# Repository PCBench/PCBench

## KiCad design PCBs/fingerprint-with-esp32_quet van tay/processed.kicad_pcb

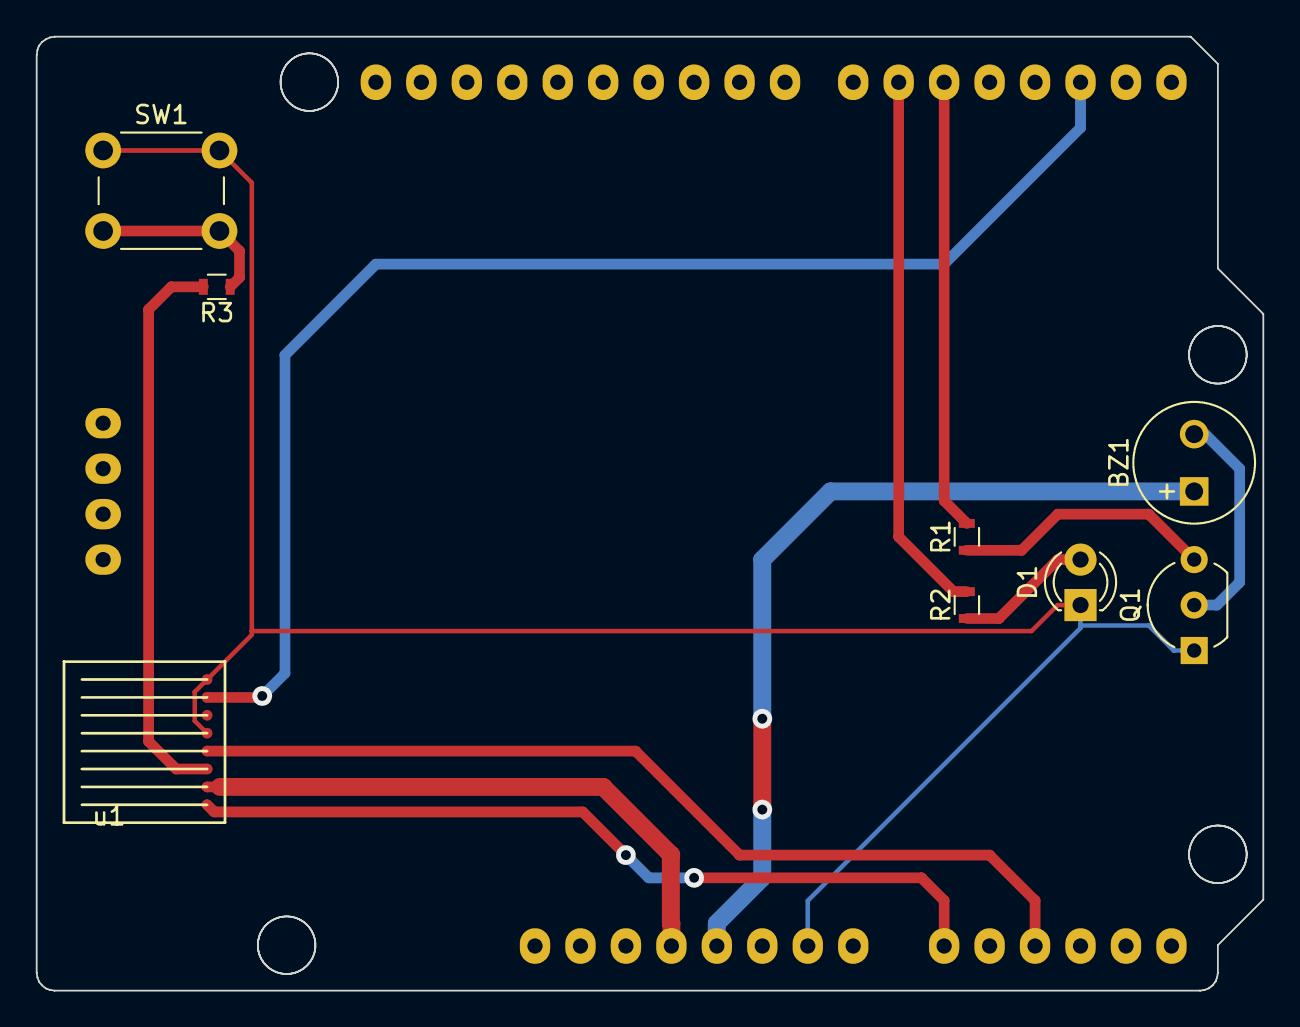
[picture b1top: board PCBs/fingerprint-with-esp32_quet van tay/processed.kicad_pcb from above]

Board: 2 copper layers, 68.5 x 53.3 mm, 9 parts (0 on the bottom side), 13 nets.

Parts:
BZ1: Buzzer; MagneticBuzzer_Kingstate_KCG0601
D1: LED; LED_D3.0mm
Q1: 2SC1815; TO-92_Inline_Wide
R1, R2: 330; R_0603
R3: 470; R_0603
S1: ESP-UNO; ESP-UNO-SH
SW1: SW_Push; SW_PUSH_6mm_h5mm
u1: fpc1011f; Pin_Header_Angled_1x08_Pitch1.27mm

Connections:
3.3V: S1.4, u1.2
5V: BZ1.1, S1.5
CLK: S1.11, u1.4
CMD: S1.17, u1.7
GND: D1.1, Q1.1, S1.7, SW1.1, u1.5, u1.8
unnamed: BZ1.2, Q1.2
unnamed: D1.2, R2.1
unnamed: Q1.3, R1.1
unnamed: R3.1, SW1.2
RST: R3.2, u1.3
SDO: S1.9, u1.1
led: R2.2, S1.21
loa: R1.2, S1.20

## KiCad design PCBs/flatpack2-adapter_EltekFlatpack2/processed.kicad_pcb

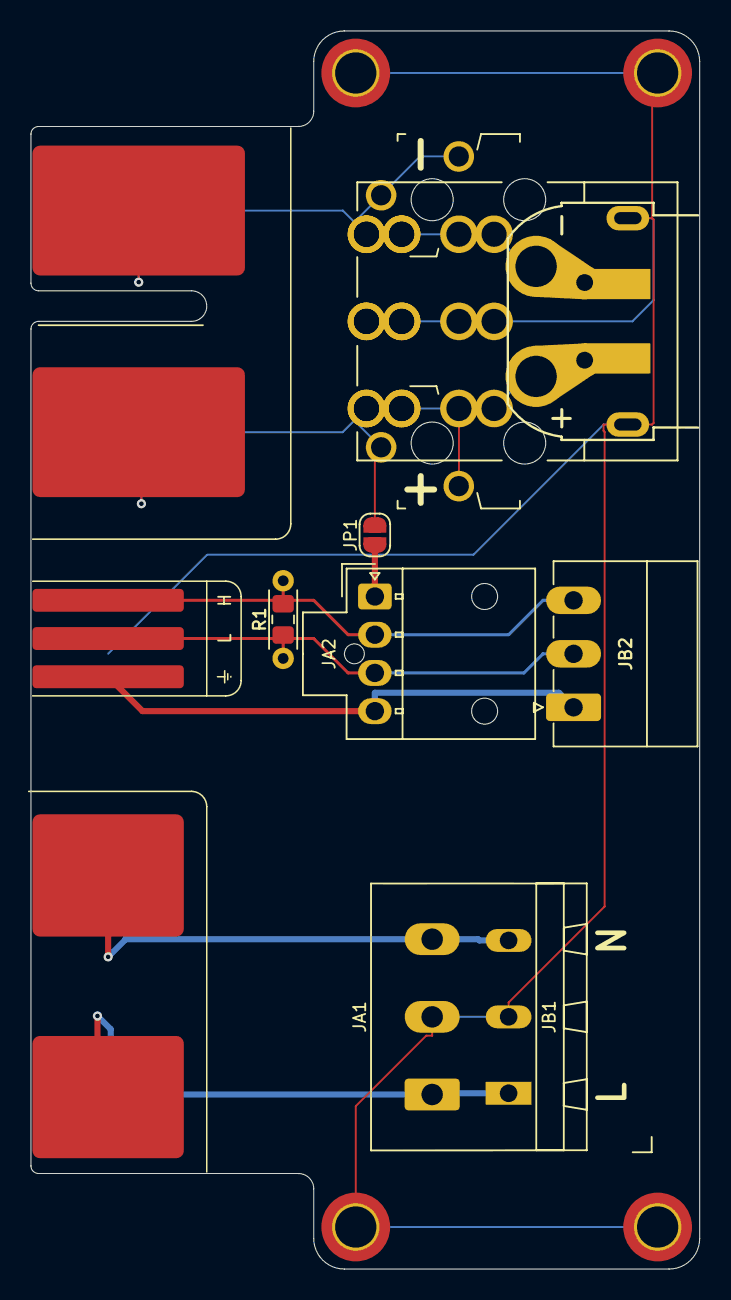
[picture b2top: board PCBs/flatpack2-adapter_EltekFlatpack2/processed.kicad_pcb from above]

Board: 2 copper layers, 43.8 x 81.0 mm, 17 parts (0 on the bottom side), 9 nets.

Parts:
H1, H2, H3, H4: M3; MountingHole_2.7mm_M2.5_ISO7380_Pad_TopBottom
JA1: AC_IN; 1605540000
JA2: CTRL; Molex_Nano-Fit_105309-xx04_1x04_P2.50mm_Combi_3D-V
JA3: DC OUT; TE_2204529-1
JB1: AC_IN; TerminalBlock_WAGO_236-103_1x03_P5.00mm_PadsOnly
JB2: CANBUS; PhoenixContact_MC_1,5_3-G-3.5_1x03_P3.50mm_Horizontal
JB3: DC OUT; TE_2204535-1
JC3: DC OUT; Amass_XT60PW-M_Kombifootprint
JP1: CTRL_VBUS+; SolderJumper-2_P1.3mm_Open_RoundedPad1.0x1.5mm
PC1: Flatpack2; CON_Edge_Flatpack2_AllContacts
R1: 120R; R_0805_2012Metric_Pad1.15x1.40mm_HandSolder
R2: 120R; R_Axial_DIN0204_L3.6mm_D1.6mm_P5.08mm_Horizontal
T1, T2: Keystone 4912; Connector_Keystone_4912_Overlaid

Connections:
/CAN+: JA2.2, JB2.3, PC1.CAN-H, R1.2, R2.2
/CAN-: JA2.3, JB2.2, PC1.CAN-L, R1.1, R2.1
/VBUS+: JA3.1, JB3.1, JB3.4, JC3.2, JP1.1, PC1.DC-POS, T1.1
/VBUS-: JA3.3, JB3.3, JB3.6, JC3.1, PC1.DC-NEG, T2.1
/VCCD: JA2.1, JP1.2
Earth: H1.1, H2.1, H3.1, H4.1, JA1.2, JA3.2, JB1.2, JB3.2, JB3.5, JC3.MP, PC1.AC-E
GNDD: JA2.4, JB2.1, PC1.GNDD
LINE: JA1.1, JB1.1, PC1.AC-L
NEUT: JA1.3, JB1.3, PC1.AC-N

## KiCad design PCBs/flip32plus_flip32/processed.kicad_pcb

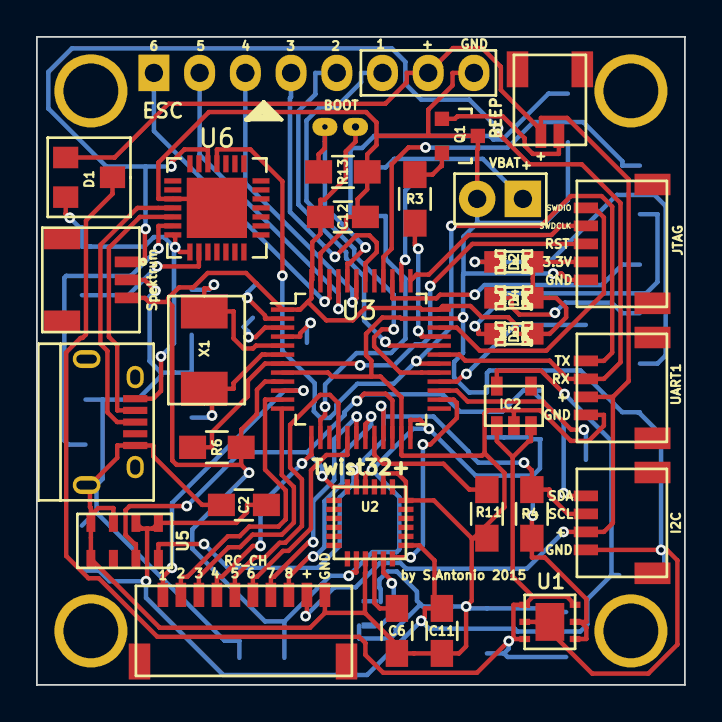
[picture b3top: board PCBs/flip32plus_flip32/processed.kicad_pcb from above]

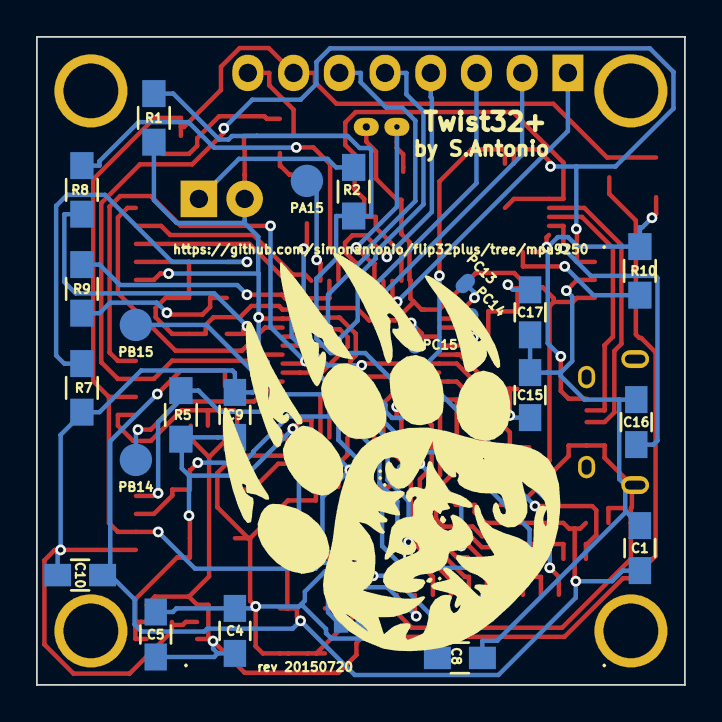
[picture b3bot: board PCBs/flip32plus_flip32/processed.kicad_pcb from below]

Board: 2 copper layers, 36.0 x 36.0 mm, 59 parts (24 on the bottom side), 54 nets.

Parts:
BEEP: BEEPER; Pin_Header_Straight_1x02
BOOT: BOOT; Pin_Header_Straight_1x02
C1, C2, C4, C5, C6, C9, C12, C16: 0.1uF; C_0805_HandSoldering
C8: 10uF; C_0805_HandSoldering
C10, C11, C15, C17: C; C_0805_HandSoldering
CON1: USB; USB_Micro-B
D1: BAV23C; GS3
D2: B; LED-0805
D3: R; LED-0805
D4: G; LED-0805
ESC: ESC OUT; Pin_Header_Straight_1x08
FSYNC-MPU: MPU-JMP; NetTie-I_Connected
I2C: I2C; Pin_Header_Straight_1x04
IC2: MIC5205; SOT-23-5
JP1: MPU-JMP; NetTie-I_Connected
JTAG: JTAG; Pin_Header_Straight_1x05
MNT1, MNT2, MNT3, MNT4: 1pin
PA15: TP; 1pin
PB14, PB15: TP; 1pin
PC13, PC14, PC15: UU5; 1pin
Q1: MMBT29; SOT-23
R1: 11K; R_0805_HandSoldering
R2, R4, R5: 1K; R_0805_HandSoldering
R3: 100; R_0805_HandSoldering
R6, R10: 10k; R_0805_HandSoldering
R7, R8, R9: R; R_0805_HandSoldering
R11, R13: 1k; R_0805_HandSoldering
RC_CH: RECV CHANNELS; Pin_Header_Straight_1x10
Spektrum: Spektrum Satellite Receiver; Pin_Header_Straight_1x03
U1: LP38691; sc70-5
U2: MPU-9250; QFN-24-1EP_3x3mm_Pitch0.4mm
U3: STM32F103CB; LQFP-48_7x7mm_Pitch0.5mm
U5: MS5611-01BA; SOIC-8_3.9x4.9mm_Pitch1.27mm
U6: CP2102; QFN-28-1EP_5x5mm_Pitch0.5mm
UART1: UART 1; Pin_Header_Straight_1x04
VBAT: VBAT; Socket_Strip_Straight_1x02
X1: 8MHZ; Q_49U3HMS

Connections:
/BOOT0: BOOT.1, R13.1, U3.44
/BOOT1: R11.1, U3.20
/LED0: R8.2, U3.40
/LED1: R9.2, U3.39
/MPU_INT: U2.12, U3.26
/NRST: JTAG.3, R6.2, U3.7
/OSC_IN: C17.1, U3.5, X1.2
/OSC_OUT: C15.1, U3.6, X1.1
/POWER_ADC: R1.2, R2.1, U3.14
/PWM1: ESC.6, U3.29
/PWM2: ESC.5, U3.32
/PWM3: ESC.4, U3.42
/PWM4: ESC.3, U3.43
/PWM5: ESC.2, U3.45
/PWM6: ESC.1, U3.46
/RC_CH1: RC_CH.1, U3.10
/RC_CH2: RC_CH.2, U3.11
/RC_CH3: RC_CH.3, U3.12
/RC_CH4: RC_CH.4, U3.13
/RC_CH5: RC_CH.5, U3.16
/RC_CH6: RC_CH.6, U3.17
/RC_CH7: RC_CH.7, U3.18
/RC_CH8: RC_CH.8, U3.19
/RX0: Spektrum.1, U3.31, U6.26, UART1.2
/SCL: I2C.2, R4.2, U2.23, U3.21, U5.8
/SDA: I2C.1, R5.2, U2.24, U3.22, U5.7
/SWDCLK: JTAG.2, U3.37
/SWDIO: JTAG.1, U3.34
/TO_REGS: C4.1, C5.1, D1.3, IC2.1, IC2.3, U1.1, U1.3, U1.6
/TX0: U3.30, U6.25, UART1.1
/UU1: R3.1, U3.33
/UU2: PA15.1, U3.38
/UU3: PC13.1, U3.2
/UU4: PC14.1, U3.3
/UU5: PC15.1, U3.4
/UU7: PB14.1, U3.27
/UU8: PB15.1, U3.28
/VBUS: CON1.1, D1.2, R10.1, U6.7, U6.8
/VCC_IN: BEEP.1, D1.1, ESC.7, I2C.3, RC_CH.9, UART1.3
/VCC_SEN: C1.1, C2.1, C10.1, C11.1, IC2.5, U2.13, U5.1, U5.2
GND: C1.2, C2.2, C4.2, C5.2, C6.2, C8.2, C9.2, C10.2, C11.2, C12.2, C15.2, C16.2, C17.2, CON1.5, CON1.6, ESC.8, FSYNC-MPU.2, I2C.4, IC2.2, JP1.2, JTAG.5, Q1.3, R1.1, R7.2, R11.2, R13.2, RC_CH.10, Spektrum.2, U1.2, U1.7, U2.9, U2.18, U2.20, U3.8, U3.23, U3.35, U3.47, U5.3, U5.4, U5.5, U6.3, U6.29, UART1.4, VBAT.2
unnamed: R10.2, U6.9
unnamed: CON1.2, U6.5
unnamed: CON1.3, U6.4
unnamed: C6.1, U2.10
unnamed: FSYNC-MPU.1, U2.11
unnamed: C16.1, U6.6
unnamed: D3.2, R8.1
unnamed: D4.2, R9.1
unnamed: D2.2, R7.1
unnamed: Q1.2, R3.2
unnamed: BEEP.2, Q1.1
unnamed: R2.2, VBAT.1
VCC: BOOT.2, C8.1, C9.1, C12.1, D2.1, D3.1, D4.1, JTAG.4, R4.1, R5.1, R6.1, Spektrum.3, U1.4, U1.5, U2.8, U2.22, U3.1, U3.9, U3.24, U3.36, U3.48

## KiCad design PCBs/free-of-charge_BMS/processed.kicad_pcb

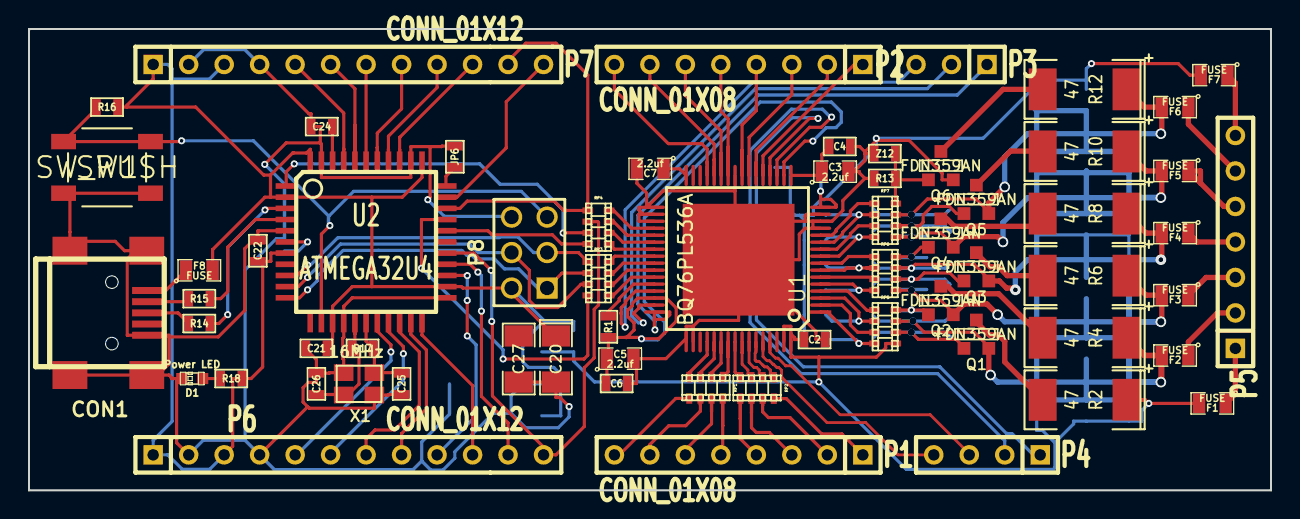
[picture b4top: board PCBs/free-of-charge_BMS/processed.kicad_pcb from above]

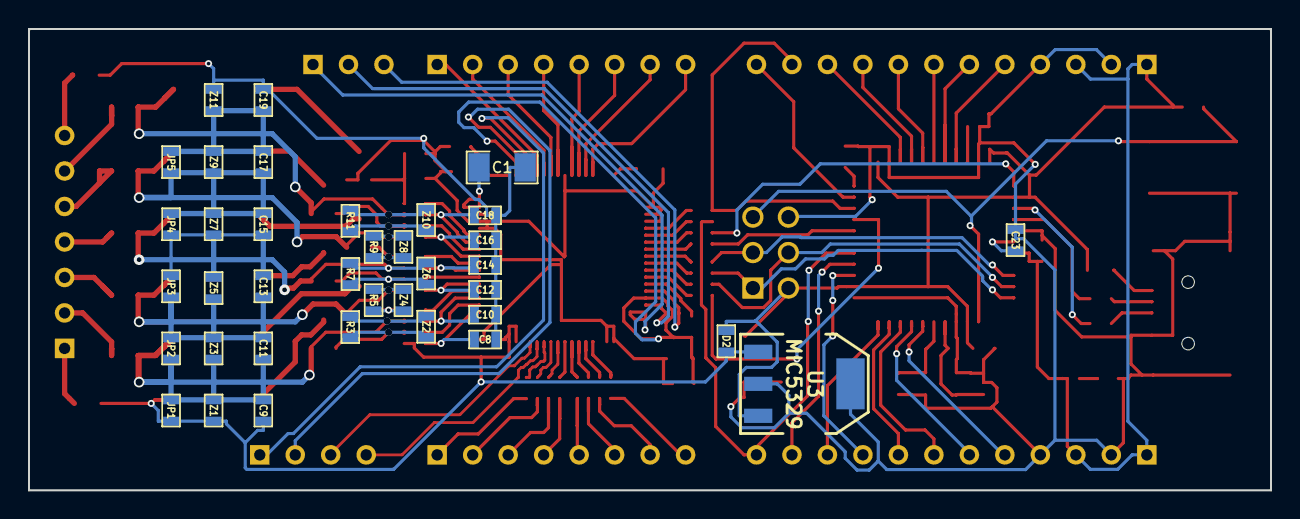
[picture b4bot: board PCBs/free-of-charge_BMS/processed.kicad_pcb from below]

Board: 2 copper layers, 88.9 x 33.0 mm, 100 parts (37 on the bottom side), 118 nets.

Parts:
C1, C27: 10uf; SM1206
C2, C4, C6, C8, C9, C10, C11, C12, C13, C14, C15, C16, C17, C18, C19, C21, C22, C24: 0.1uf; SM0603
C3, C5, C7: 2.2uf; SM0805
C20: 10uf; SM1206POL
C23: 1uf; SM0603
C25, C26: 20pf; SM0603
CON1: USB-MINI-B; USB_MINI_B
D1: Power LED; LED-0603
D2: DIODE; SM0603
F1, F2, F3, F4, F5, F6, F7, F8: FUSE; SM0805
JP1, JP2, JP3, JP4, JP5, JP6: JUMPER; SM0603
P1, P2: CONN_01X08; SIL-8
P3: CONN_01X03; SIL-3
P4: CONN_01X04; SIL-4
P5: CONN_01X07; SIL-7
P6, P7: CONN_01X12; SIL-12
P8: CONN_02X03; pin_array_3x2
Q1, Q2, Q3, Q4, Q5, Q6: FDN359AN; SOT23GDS
R1: 100k; SM0603
R2, R4, R6, R8, R10, R12: 47; SM2512
R3, R5, R7, R9, R11, R13: 1M 1%; SM0603
R14, R15: 22; SM0603
R16: 10k; SM0603
R17: 1M; SM0603
R18: 1k; SM0603
RP1, RP2, RP3, RP4: R_PACK4; r_cat16-4
RP5, RP6, RP7: 1k; r_cat16-4
SW1: SW_PUSH; SW
U1: BQ76PL536A; HTQFP_64
U2: ATMEGA32U4; TQFP44
U3: MIC5329; SOT223
X1: 16MHz; crystal_FA238-TSX3225
Z1, Z2, Z3, Z4, Z5, Z6, Z7, Z8, Z9, Z10, Z11, Z12: ZENER; SM0603

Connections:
+5V: C20.1, C21.1, C22.1, D2.1, F8.2, P6.1, P6.3, P7.1, P7.3, P8.2, R16.1, R18.2, U2.2, U2.7, U2.14, U2.24, U2.34, U2.44, U3.3
+BATT: C2.1, C9.1, D2.2, F1.2, JP1.1, R2.1, RP5.1, U1.63, U1.64, U3.1, Z1.2
/CellBallance/C0: F7.1, P5.7
/CellBallance/C1: F6.1, P5.6
/CellBallance/C2: F5.1, P5.5
/CellBallance/C3: F4.1, P5.4
/CellBallance/C4: F3.1, P5.3
/CellBallance/C5: F2.1, P5.2
/CellBallance/C6: F1.1, P5.1
/CellBallance/CB1: RP7.5, U1.12
/CellBallance/CB2: RP7.7, U1.10
/CellBallance/CB3: RP6.5, U1.8
/CellBallance/CB4: RP6.7, U1.6
/CellBallance/CB5: RP5.5, U1.4
/CellBallance/CB6: RP5.7, U1.2
/CellBallance/VC1: C18.2, RP7.6, U1.11
/CellBallance/VC2: C16.2, RP7.8, U1.9
/CellBallance/VC3: C14.2, RP6.6, U1.7
/CellBallance/VC4: C12.2, RP6.8, U1.5
/CellBallance/VC5: C10.2, RP5.6, U1.3
/CellBallance/VC6: C8.2, RP5.8, U1.1
/LDOA: C3.1, C4.1, U1.17
/LDOD: C5.1, C6.1, R1.2, U1.18, U1.46
/REG50: C7.1, U1.32
/VREF: C1.1, U1.16
/atmega32u4/A0: P7.10, U2.36
/atmega32u4/A1: P7.9, U2.37
/atmega32u4/A2: P7.8, U2.38
/atmega32u4/A3: P7.7, U2.39
/atmega32u4/A4: P7.6, U2.40
/atmega32u4/A5: P7.5, U2.41
/atmega32u4/ALERT_H: RP4.7, U2.1
/atmega32u4/AREF: C24.1, U2.42
/atmega32u4/CONV_H: P7.11, RP4.5, U2.31
/atmega32u4/CS_H: RP3.8, U2.30
/atmega32u4/D0/RX: P6.7, U2.20
/atmega32u4/D1/TX: P6.8, U2.21
/atmega32u4/D2/SDA: P6.6, U2.19
/atmega32u4/D3/SCL: P6.5, U2.18
/atmega32u4/D4: P6.9, U2.25
/atmega32u4/DRDY_H: P6.12, RP4.6, U2.27
/atmega32u4/FAULT_H: RP4.8, U2.29
/atmega32u4/HWB: JP6.1, U2.33
/atmega32u4/IO12: P6.11, U2.26
/atmega32u4/IO13*: P7.12, U2.32
/atmega32u4/RST: P8.5, R16.2, SW1.2, U2.13
/atmega32u4/SCLK_H: P8.3, RP3.5, U2.9
/atmega32u4/SDI_H: P8.4, RP3.7, U2.10
/atmega32u4/SDO_H: P8.1, RP3.6, U2.11
/atmega32u4/TXLED: P6.10, U2.22
/atmega32u4/UCAP: C23.1, U2.6
GND: C20.2, C21.2, C22.2, C23.2, C24.2, C25.2, C26.2, C27.2, CON1.5, CON1.6, CON1.7, CON1.8, CON1.9, D1.2, JP6.2, P6.2, P6.4, P7.2, P7.4, P8.6, SW1.1, U2.5, U2.15, U2.23, U2.35, U2.43, U3.2, U3.4, X1.3
unnamed: P2.1, U1.21
unnamed: P2.2, U1.22
unnamed: P2.3, U1.23
unnamed: P2.4, U1.24
unnamed: P2.5, U1.26
unnamed: P2.6, U1.27
unnamed: P1.3, RP2.2
unnamed: P1.2, RP2.3
unnamed: P1.1, RP2.4
unnamed: P1.4, RP2.1
unnamed: P2.7, U1.28
unnamed: P2.8, U1.29
unnamed: P1.5, RP1.4
unnamed: P1.6, RP1.3
unnamed: P1.7, RP1.2
unnamed: P1.8, RP1.1
unnamed: P3.2, U1.47
unnamed: RP1.8, U1.52
unnamed: RP1.7, U1.53
unnamed: RP1.6, U1.54
unnamed: RP1.5, U1.55
unnamed: P3.3, U1.45
unnamed: P3.1, U1.48
unnamed: P4.4, U1.60
unnamed: P4.3, U1.61
unnamed: P4.2, U1.19
unnamed: RP3.4, U1.40
unnamed: RP3.3, U1.41
unnamed: RP3.2, U1.42
unnamed: RP3.1, U1.43
unnamed: P4.1, U1.20
unnamed: RP4.4, U1.36
unnamed: RP4.3, U1.37
unnamed: RP4.2, U1.38
unnamed: RP4.1, U1.39
unnamed: RP2.8, U1.56
unnamed: RP2.7, U1.57
unnamed: RP2.6, U1.58
unnamed: RP2.5, U1.59
unnamed: R1.1, U1.44
unnamed: Q1.G, R3.1, RP5.2, Z2.2
unnamed: Q1.D, R2.2
unnamed: Q2.D, R4.2
unnamed: Q6.G, R13.1, RP7.4, Z12.2
unnamed: Q4.G, R9.1, RP6.4, Z8.2
unnamed: Q5.D, R10.2
unnamed: Q5.G, R11.1, RP7.2, Z10.2
unnamed: Q3.G, R7.1, RP6.2, Z6.2
unnamed: C13.2, C15.1, F4.2, JP3.2, JP4.1, Q3.S, R7.2, R8.1, RP6.3, Z5.1, Z6.1, Z7.2
unnamed: Q2.G, R5.1, RP5.4, Z4.2
unnamed: C15.2, C17.1, F5.2, JP4.2, JP5.1, Q4.S, R9.2, R10.1, RP7.1, Z7.1, Z8.1, Z9.2
unnamed: C17.2, C19.1, F6.2, JP5.2, Q5.S, R11.2, R12.1, RP7.3, Z9.1, Z10.1, Z11.2
unnamed: Q6.D, R12.2
unnamed: C11.2, C13.1, F3.2, JP2.2, JP3.1, Q2.S, R5.2, R6.1, RP6.1, Z3.1, Z4.1, Z5.2
unnamed: C9.2, C11.1, F2.2, JP1.2, JP2.1, Q1.S, R3.2, R4.1, RP5.3, Z1.1, Z2.1, Z3.2
unnamed: Q4.D, R8.2
unnamed: Q3.D, R6.2
unnamed: CON1.1, F8.1
unnamed: R15.2, U2.4
unnamed: R14.2, U2.3
unnamed: CON1.2, R15.1
unnamed: C26.1, R17.2, U2.16, X1.2
unnamed: C25.1, R17.1, U2.17, X1.1
unnamed: D1.1, R18.1
unnamed: CON1.3, R14.1
VSS: C1.2, C2.2, C3.2, C4.2, C5.2, C6.2, C7.2, C8.1, C10.1, C12.1, C14.1, C16.1, C18.1, C19.2, F7.2, Q6.S, R13.2, U1.0, U1.13, U1.14, U1.15, U1.25, U1.33, U1.34, U1.35, U1.49, U1.50, Z11.1, Z12.1

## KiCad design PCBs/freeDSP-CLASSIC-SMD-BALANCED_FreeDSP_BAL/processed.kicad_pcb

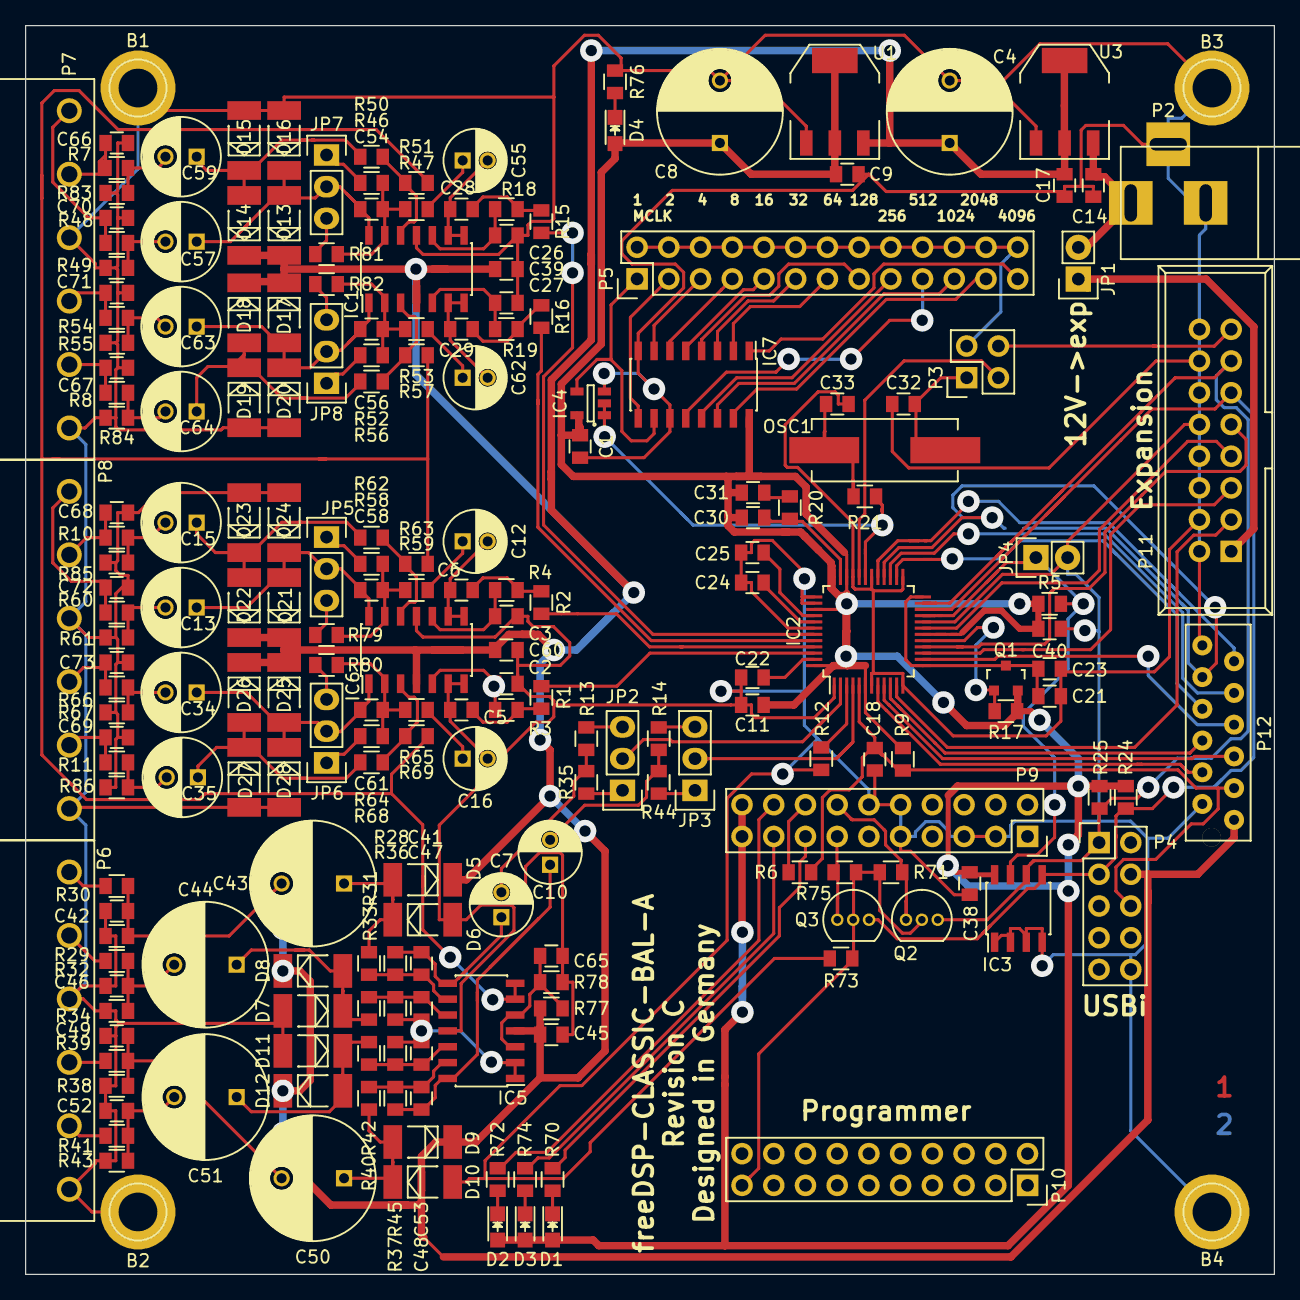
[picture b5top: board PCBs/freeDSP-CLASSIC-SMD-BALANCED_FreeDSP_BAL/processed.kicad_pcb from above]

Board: 2 copper layers, 100.0 x 100.0 mm, 215 parts (0 on the bottom side), 148 nets.

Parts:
B1, B2, B3, B4: TEST_1P; 1pin
C1, C17, C23, C38, C39, C40, C45, C60: 100n; C0805-X7R
C2, C3, C26, C27: 150p; C0805-X7R
C4, C8: 220u./35V; C_Radial_D10_L13_P5
C5, C6, C28, C29: 470p; C0805-X7R
C7, C10, C12, C16, C55, C62: 100u./16V; C_Radial_D5_L11_P2
C9, C11, C14, C21, C22, C24, C25: 10u0; C0805-X7R
C13, C15, C34, C35, C57, C59, C63, C64: 47u0./50V; C_Radial_D6.3_L11.2_P2.5
C18: 10n0; C0805-X7R
C30: 3n30; C0805-X7R
C31: 56n0; C0805-X7R
C32, C33: 22p0; C0805-X7R
C41, C47, C48, C53: 27p0; C0805-X7R
C42, C46, C49, C52: 100p; C0805-X7R
C43, C44, C50, C51: 47u0./63V; C_Radial_D10_L16_P5
C54, C56, C58, C61: 47p0; C0805-X7R
C65: 22u0./X5R; C0805-X7R
C66, C67, C68, C69, C70, C71, C72, C73: 2n20; C0805-X7R
D1, D4: GREEN; LED_0805
D2, D3: RED; LED_0805
D5, D6, D7, D8, D9, D10, D11, D12, D13, D14, D15, D16, D17, D18, D19, D20, D21, D22, D23, D24, D25, D26, D27, D28: LL4002; MELF_Standard
IC1, IC5, IC6: AD8608ARZ; SOIC-14_3.9x8.7mm_Pitch1.27mm
IC2: ADAU1701; LQFP-48_7x7mm_Pitch0.5mm
IC3: 24AA256; SOIC-8_3.9x4.9mm_Pitch1.27mm
IC4: SN74LVC1G08DBVR; SOT-23-5
IC7: 74HC4040D; SOIC-16_3.9x9.9mm_Pitch1.27mm
JP1, JP4: JUMPER; Pin_Header_Straight_1x02
JP2, JP3, JP5, JP6, JP7, JP8: JUMPER3; Pin_Header_Straight_1x03
OSC1: 24M576Hz; Crystal_HC49-SD_SMD
P2: BARREL_JACK
P3: CONN_02X02; Pin_Header_Straight_2x02
P4: USBi; Pin_Header_Straight_2x05
P5: CONN_02X13; Pin_Header_Straight_2x13
P6, P7, P8: CONN_01X06; SL_5.08HC-06-90
P9, P10: CONN_02X10; Socket_Strip_Straight_2x10
P11: IDC-16G; IDC_Header_Straight_16pins
P12: MM-12G
Q1: ZXTP25040DFHTA; SOT-23
Q2, Q3: 2N7000; TO-92_Inline_Narrow_Oval
R1, R2, R3, R4, R15, R16, R18, R19: 4K75; C0805-RES
R5, R24, R25, R28, R36, R37, R45, R47, R53, R59, R65, R71, R75: 10K0; C0805-RES
R6, R20, R70, R72, R74, R76: 470R; C0805-RES
R7, R8, R10, R11, R48, R54, R60, R66: 56R0; C0805-RES
R9, R12: 18K0; C0805-RES
R13, R14: 9K09; C0805-RES
R17: 1K00; C0805-RES
R21, R30, R32, R39, R41: 100R; C0805-RES
R29, R34, R38, R43, R83, R84, R85, R86: 100K; C0805-RES
R31, R33, R40, R42: 14K0; C0805-RES
R35, R44: 261R; C0805-RES
R46, R52, R58, R64: 3K57; C0805-RES
R49, R55, R61, R67: 22K0; C0805-RES
R50, R51, R56, R57, R62, R63, R68, R69: 27R0; C0805-RES
R73: 1M00; C0805-RES
R77, R78: 47K0; C0805-RES
R79, R80, R81, R82: 17K4; C0805-RES
U1: 78033; SOT-223_Reg_MAE
U3: 7805; SOT-223_Reg_MAE

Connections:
3V3: C1.1, C8.1, C9.1, C11.1, C30.1, C31.1, C38.1, C40.1, D1.2, D2.2, D3.2, D4.2, IC2.6, IC2.18, IC2.34, IC2.36, IC2.39, IC2.48, IC3.8, IC4.5, IC7.16, P9.19, P9.20, Q1.2, R5.2, R9.2, R17.2, R24.2, R25.2, U1.VO
+5V: C4.1, C17.1, C39.2, C45.2, C60.2, D5.1, D8.1, D9.1, D12.1, D13.1, D14.1, D17.1, D18.1, D21.1, D22.1, D25.1, D26.1, IC1.4, IC5.4, IC6.4, P4.4, P12.1, R77.1, U1.VI, U3.VO
/DAC1: IC2.46, R1.2
/DAC2: IC2.45, R2.2
/DAC3: IC2.44, R16.2
/DAC4: IC2.43, R15.2
/IN1: IC2.2, JP2.2
/IN1+: P6.1, R30.2
/IN1-: P6.2, R32.2
/IN2: IC2.4, JP3.2
/IN2+: P6.4, R39.2
/IN2-: P6.5, R41.2
/OUT1+: C70.2, P7.1, R48.1
/OUT1-: C66.1, P7.2, R7.1
/OUT2+: C71.2, P7.4, R54.1
/OUT2-: C67.1, P7.5, R8.1
/OUT3+: C72.2, P8.1, R60.1
/OUT3-: C68.1, P8.2, R10.1
/OUT4+: C73.2, P8.4, R66.1
/OUT4-: C69.1, P8.5, R11.1
/USB_LED1: P9.15, R70.2
/USB_LED2: P9.18, R72.2
/USB_LED3: P9.17, R74.2
/USB_PWR_ON: P10.19, Q2.2, Q3.2, R71.2, R73.2, R75.1
/USB_SCL: P9.14, Q2.1, R71.1
/USB_SDA: P9.13, Q3.1, R75.2
/VO1: C47.2, C53.2, IC5.1, IC5.2, R36.2, R45.2
/VO2: IC5.6, IC5.7, R51.2, R57.2, R63.1, R69.2
/WP: IC2.21, IC3.7, JP4.1, R5.1
BCLK: IC2.19, P11.7
GND: B1.1, B2.1, B3.1, B4.1, C1.2, C2.1, C3.1, C4.2, C8.2, C9.2, C11.2, C14.2, C17.2, C18.2, C21.2, C22.2, C23.2, C24.2, C25.2, C26.1, C27.1, C32.2, C33.2, C38.2, C39.1, C40.2, C42.1, C45.1, C46.1, C49.1, C52.1, C60.1, C65.1, C66.2, C67.2, C68.2, C69.2, C70.1, C71.1, C72.1, C73.1, D6.2, D7.2, D10.2, D11.2, D15.2, D16.2, D19.2, D20.2, D23.2, D24.2, D27.2, D28.2, IC1.11, IC2.1, IC2.7, IC2.12, IC2.20, IC2.25, IC2.30, IC2.33, IC2.37, IC2.38, IC2.42, IC3.1, IC3.2, IC3.3, IC3.4, IC4.3, IC5.11, IC6.11, IC7.8, IC7.11, JP4.2, P2.2, P2.3, P4.10, P6.3, P6.6, P7.3, P7.6, P8.3, P8.6, P9.3, P9.5, P9.9, P9.10, P9.12, P11.2, P11.4, P11.6, P11.8, P11.10, P11.12, P11.14, P11.16, P12.2, P12.12, R12.1, R29.1, R34.1, R38.1, R43.1, R49.2, R55.2, R61.2, R67.2, R73.1, R76.2, R78.2, R83.2, R84.2, R85.2, R86.2, U1.GND, U3.GND
LRCLK: IC2.16, P11.9
MCLK: P3.4, P11.15
MDI: IC2.11, P11.3
MDO: IC2.15, P11.5
MP1: IC2.10, P12.6
MP2: IC2.29, P12.11
MP3: IC2.28, P12.10
MP4: IC2.8, P12.4
MP5: IC2.9, P12.5
MP7: IC2.14, P12.7
MP8: IC2.27, P12.9
MP9: IC2.26, P12.8
unnamed: C2.2, IC6.5, R3.1
unnamed: C3.2, IC6.10, R4.1
unnamed: C5.2, R1.1, R3.2
unnamed: C6.2, R2.1, R4.2
unnamed: C7.2, R13.1, R35.2
unnamed: C10.1, C48.1, IC5.14, R37.1
unnamed: C10.2, R14.1, R44.2
unnamed: C12.1, R59.2
unnamed: C6.1, C12.2, IC6.8, IC6.9
unnamed: C13.1, C58.1, D21.2, D24.1, IC6.14, JP5.2
unnamed: C13.2, R60.2, R61.1
unnamed: C15.1, D22.2, D23.1, R62.1
unnamed: C15.2, R10.2, R85.1
unnamed: C16.1, R65.2
unnamed: C5.1, C16.2, IC6.6, IC6.7
unnamed: C21.1, C23.1, IC2.13, IC2.24, Q1.3
unnamed: C22.1, IC2.47
unnamed: C24.1, IC2.41
unnamed: C25.1, IC2.40
unnamed: C26.2, IC1.10, R18.1
unnamed: C27.2, IC1.5, R19.1
unnamed: C28.1, C55.2, IC1.8, IC1.9
unnamed: C28.2, R15.1, R18.2
unnamed: C29.1, C62.2, IC1.6, IC1.7
unnamed: C29.2, R16.1, R19.2
unnamed: C30.2, IC2.35, R20.2
unnamed: C31.2, R20.1
unnamed: C32.1, OSC1.2, P3.1
unnamed: C33.1, OSC1.1, R21.2
unnamed: C34.1, C61.1, D25.2, D28.1, IC6.1, JP6.2
unnamed: C34.2, R66.2, R67.1
unnamed: C35.1, D26.2, D27.1, R68.1
unnamed: C35.2, R11.2, R86.1
unnamed: C7.1, C41.1, IC5.8, R28.1
unnamed: C41.2, IC5.9, R28.2, R31.1
unnamed: C42.2, C43.2, R29.2, R30.1
unnamed: C43.1, D5.2, D6.1, R31.2
unnamed: C44.1, D7.1, D8.2, R33.2
unnamed: C44.2, C46.2, R32.1, R34.2
unnamed: C47.1, IC5.10, R33.1, R36.1
unnamed: C48.2, IC5.13, R37.2, R40.1
unnamed: C49.2, C50.2, R38.2, R39.1
unnamed: C50.1, D9.2, D10.1, R40.2
unnamed: C51.1, D11.1, D12.2, R42.2
unnamed: C51.2, C52.2, R41.1, R43.2
unnamed: C53.1, IC5.12, R42.1, R45.1
unnamed: C54.1, C57.1, D13.2, D16.1, IC1.14, JP7.2
unnamed: C54.2, IC1.13, R46.2, R47.1, R81.2
unnamed: C55.1, R47.2
unnamed: C56.1, C63.1, D17.2, D20.1, IC1.1, JP8.2
unnamed: C56.2, IC1.2, R52.2, R53.1, R82.2
unnamed: C57.2, R48.2, R49.1
unnamed: C58.2, IC6.13, R58.2, R59.1, R79.2
unnamed: C59.1, D14.2, D15.1, R50.1
unnamed: C59.2, R7.2, R83.1
unnamed: C61.2, IC6.2, R64.2, R65.1, R80.2
unnamed: C62.1, R53.2
unnamed: C63.2, R54.2, R55.1
unnamed: C64.1, D18.2, D19.1, R56.1
unnamed: C64.2, R8.2, R84.1
unnamed: C65.2, IC5.3, IC5.5, R77.2, R78.1
unnamed: D1.1, R70.1
unnamed: D2.1, R72.1
unnamed: D3.1, R74.1
unnamed: D4.1, R76.1
unnamed: IC1.3, R56.2, R57.1
unnamed: IC1.12, R50.2, R51.1
unnamed: IC2.3, R12.2
unnamed: IC2.17, Q1.1, R17.1
unnamed: IC2.31, IC4.1, IC4.2, R21.1
unnamed: IC2.32, P3.3
unnamed: IC4.4, IC7.10, P5.1
unnamed: IC6.3, R68.2, R69.1
unnamed: IC6.12, R62.2, R63.2
unnamed: IC7.1, P5.25
unnamed: IC7.2, P5.13
unnamed: IC7.3, P5.11
unnamed: IC7.4, P5.15
unnamed: IC7.5, P5.9
unnamed: IC7.6, P5.7
unnamed: IC7.7, P5.5
unnamed: IC7.9, P5.3
unnamed: IC7.12, P5.19
unnamed: IC7.13, P5.17
unnamed: IC7.14, P5.21
unnamed: IC7.15, P5.23
unnamed: JP1.1, P11.1
unnamed: JP2.1, R35.1
unnamed: JP2.3, R13.2
unnamed: JP3.1, R44.1
unnamed: JP3.3, R14.2
unnamed: JP5.1, R58.1
unnamed: JP5.3, R79.1
unnamed: JP6.1, R64.1
unnamed: JP6.3, R80.1
unnamed: JP7.1, R46.1
unnamed: JP7.3, R81.1
unnamed: JP8.1, R52.1
unnamed: JP8.3, R82.1
unnamed: P3.2, P5.2, P5.4, P5.6, P5.8, P5.10, P5.12, P5.14, P5.16, P5.18, P5.20, P5.22, P5.24, P5.26
unnamed: P9.16, R6.1
SCL: IC2.23, IC3.6, P4.1, P11.13, Q2.3, R25.1
SDA: IC2.22, IC3.5, P4.3, P11.11, Q3.3, R24.1
VCC: C14.1, JP1.2, P2.1, U3.VI
_RESET: C18.1, IC2.5, P4.6, P12.3, R6.2, R9.1
